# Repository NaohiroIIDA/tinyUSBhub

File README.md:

# tinyUSBhub

## What is this?
This is tiny-USB-hub board.(no Connector 16.5mm x 18mm)
It use FE1.1s.

## PCB

## SCH

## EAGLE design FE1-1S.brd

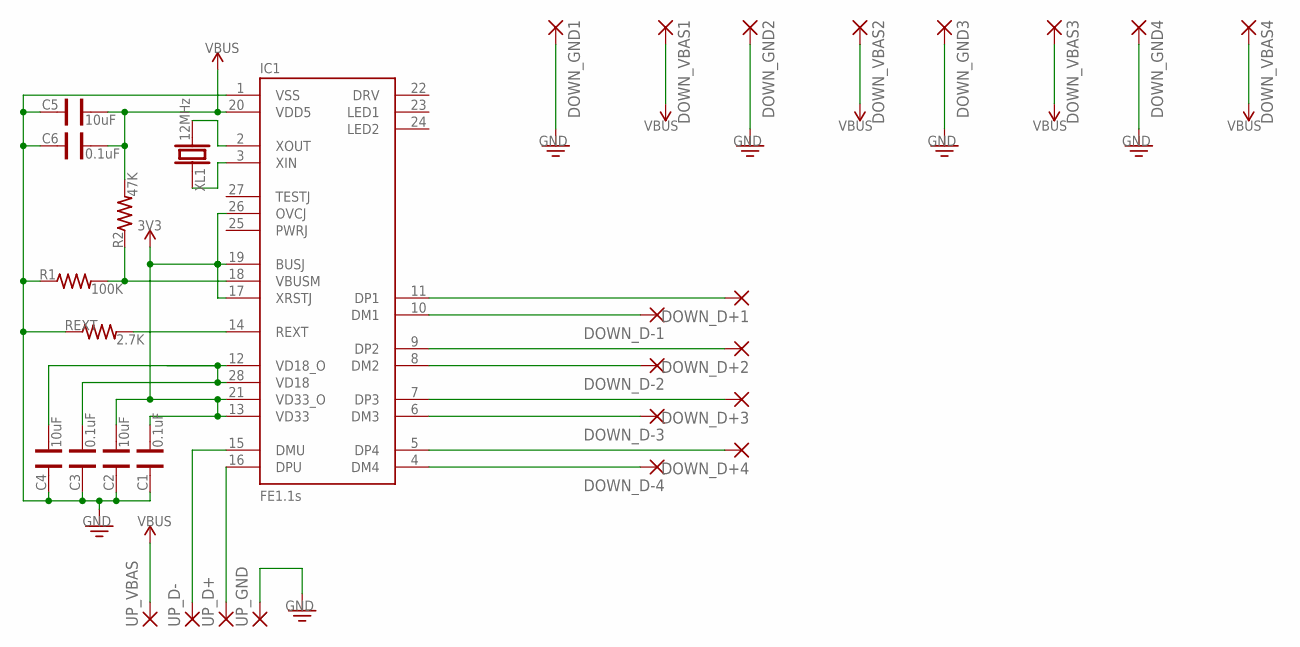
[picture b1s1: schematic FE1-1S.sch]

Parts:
C1, C3, C6: 0.1uF; CAP-0603
C2, C4, C5: 10uF; CAP-0603
DOWN_D+1, DOWN_D+2, DOWN_D+3, DOWN_D+4: SMD2; SMD1,27-2,54
DOWN_D-1, DOWN_D-2, DOWN_D-3, DOWN_D-4: SMD2; SMD1,27-2,54
DOWN_GND1, DOWN_GND2, DOWN_GND3, DOWN_GND4: SMD2; SMD1,27-2,54
DOWN_VBAS1, DOWN_VBAS2, DOWN_VBAS3, DOWN_VBAS4: SMD2; SMD1,27-2,54
IC1: FE1.1S; FE1.1S_SSOP-28
R1: 100K; RES-0603
R2: 47K; RES-0603
REXT: 2.7K; RES-0603
UP_D+: SMD2; SMD1,27-2,54
UP_D-: SMD2; SMD1,27-2,54
UP_GND: SMD2; SMD1,27-2,54
UP_VBAS: SMD2; SMD1,27-2,54
XL1: 12MHz; HC49S

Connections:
3V3: C1.1, C2.1, IC1.13 (VD33), IC1.17 (XRSTJ), IC1.19 (BUSJ), IC1.21 (VD33_O), IC1.26 (OVCJ)
DD+1: DOWN_D+1.1, IC1.11 (DP1)
DD+2: DOWN_D+2.1, IC1.9 (DP2)
DD+3: DOWN_D+3.1, IC1.7 (DP3)
DD+4: DOWN_D+4.1, IC1.5 (DP4)
DD-1: DOWN_D-1.1, IC1.10 (DM1)
DD-2: DOWN_D-2.1, IC1.8 (DM2)
DD-3: DOWN_D-3.1, IC1.6 (DM3)
DD-4: DOWN_D-4.1, IC1.4 (DM4)
GND: C1.2, C2.2, C3.2, C4.2, C5.2, C6.2, DOWN_GND1.1, DOWN_GND2.1, DOWN_GND3.1, DOWN_GND4.1, IC1.1 (VSS), R1.1, REXT.1, UP_GND.1
unnamed: IC1.14 (REXT), REXT.2
unnamed: IC1.15 (DMU), UP_D-.1
unnamed: IC1.16 (DPU), UP_D+.1
unnamed: IC1.2 (XOUT), XL1.2
unnamed: C3.1, C4.1, IC1.12 (VD18_O), IC1.28 (VD18)
unnamed: IC1.3 (XIN), XL1.1
unnamed: IC1.18 (VBUSM), R1.2, R2.1
VBUS: C5.1, C6.1, DOWN_VBAS1.1, DOWN_VBAS2.1, DOWN_VBAS3.1, DOWN_VBAS4.1, IC1.20 (VDD5), R2.2, UP_VBAS.1

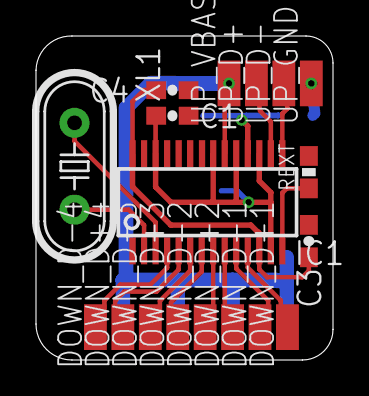
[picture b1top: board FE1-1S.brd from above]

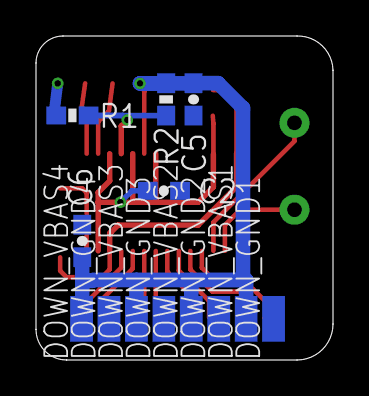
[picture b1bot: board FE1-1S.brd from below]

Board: 2 copper layers, 16.5 x 18.0 mm, 31 parts (13 on the bottom side), 18 nets.

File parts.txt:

Partlist exported from /Users/naohiroiida/Dropbox/eagle/201711sony/FE1-1S/FE1-1S.sch at 2018/02/11 22:12

Qty Value  Device       Package        Parts                                                                                                                                                                                                     Description         
20         SMD2         SMD1,27-2,54   DOWN_D+1, DOWN_D+2, DOWN_D+3, DOWN_D+4, DOWN_D-1, DOWN_D-2, DOWN_D-3, DOWN_D-4, DOWN_GND1, DOWN_GND2, DOWN_GND3, DOWN_GND4, DOWN_VBAS1, DOWN_VBAS2, DOWN_VBAS3, DOWN_VBAS4, UP_D+, UP_D-, UP_GND, UP_VBAS SMD PAD             
3   0.1uF  CAP0603      CAP-0603       C1, C3, C6                                                                                                                                                                                                                    
1   100K   RES0603      RES-0603       R1                                                                                                                                                                                                        Part # blah Digikey 
3   10uF   CAP0603      CAP-0603       C2, C4, C5                                                                                                                                                                                                                    
1   12MHz  CRYSTALHC49S HC49S          XL1                                                                                                                                                                                                       PTH: ...            
1   2.7K   RES0603      RES-0603       REXT                                                                                                                                                                                                      Part # blah Digikey 
1   47K    RES0603      RES-0603       R2                                                                                                                                                                                                        Part # blah Digikey 
1   FE1.1S FE1.1S       FE1.1S_SSOP-28 IC1

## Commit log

2018-02-11 add files
2018-02-11 fix readme
2018-02-11 fix parts
